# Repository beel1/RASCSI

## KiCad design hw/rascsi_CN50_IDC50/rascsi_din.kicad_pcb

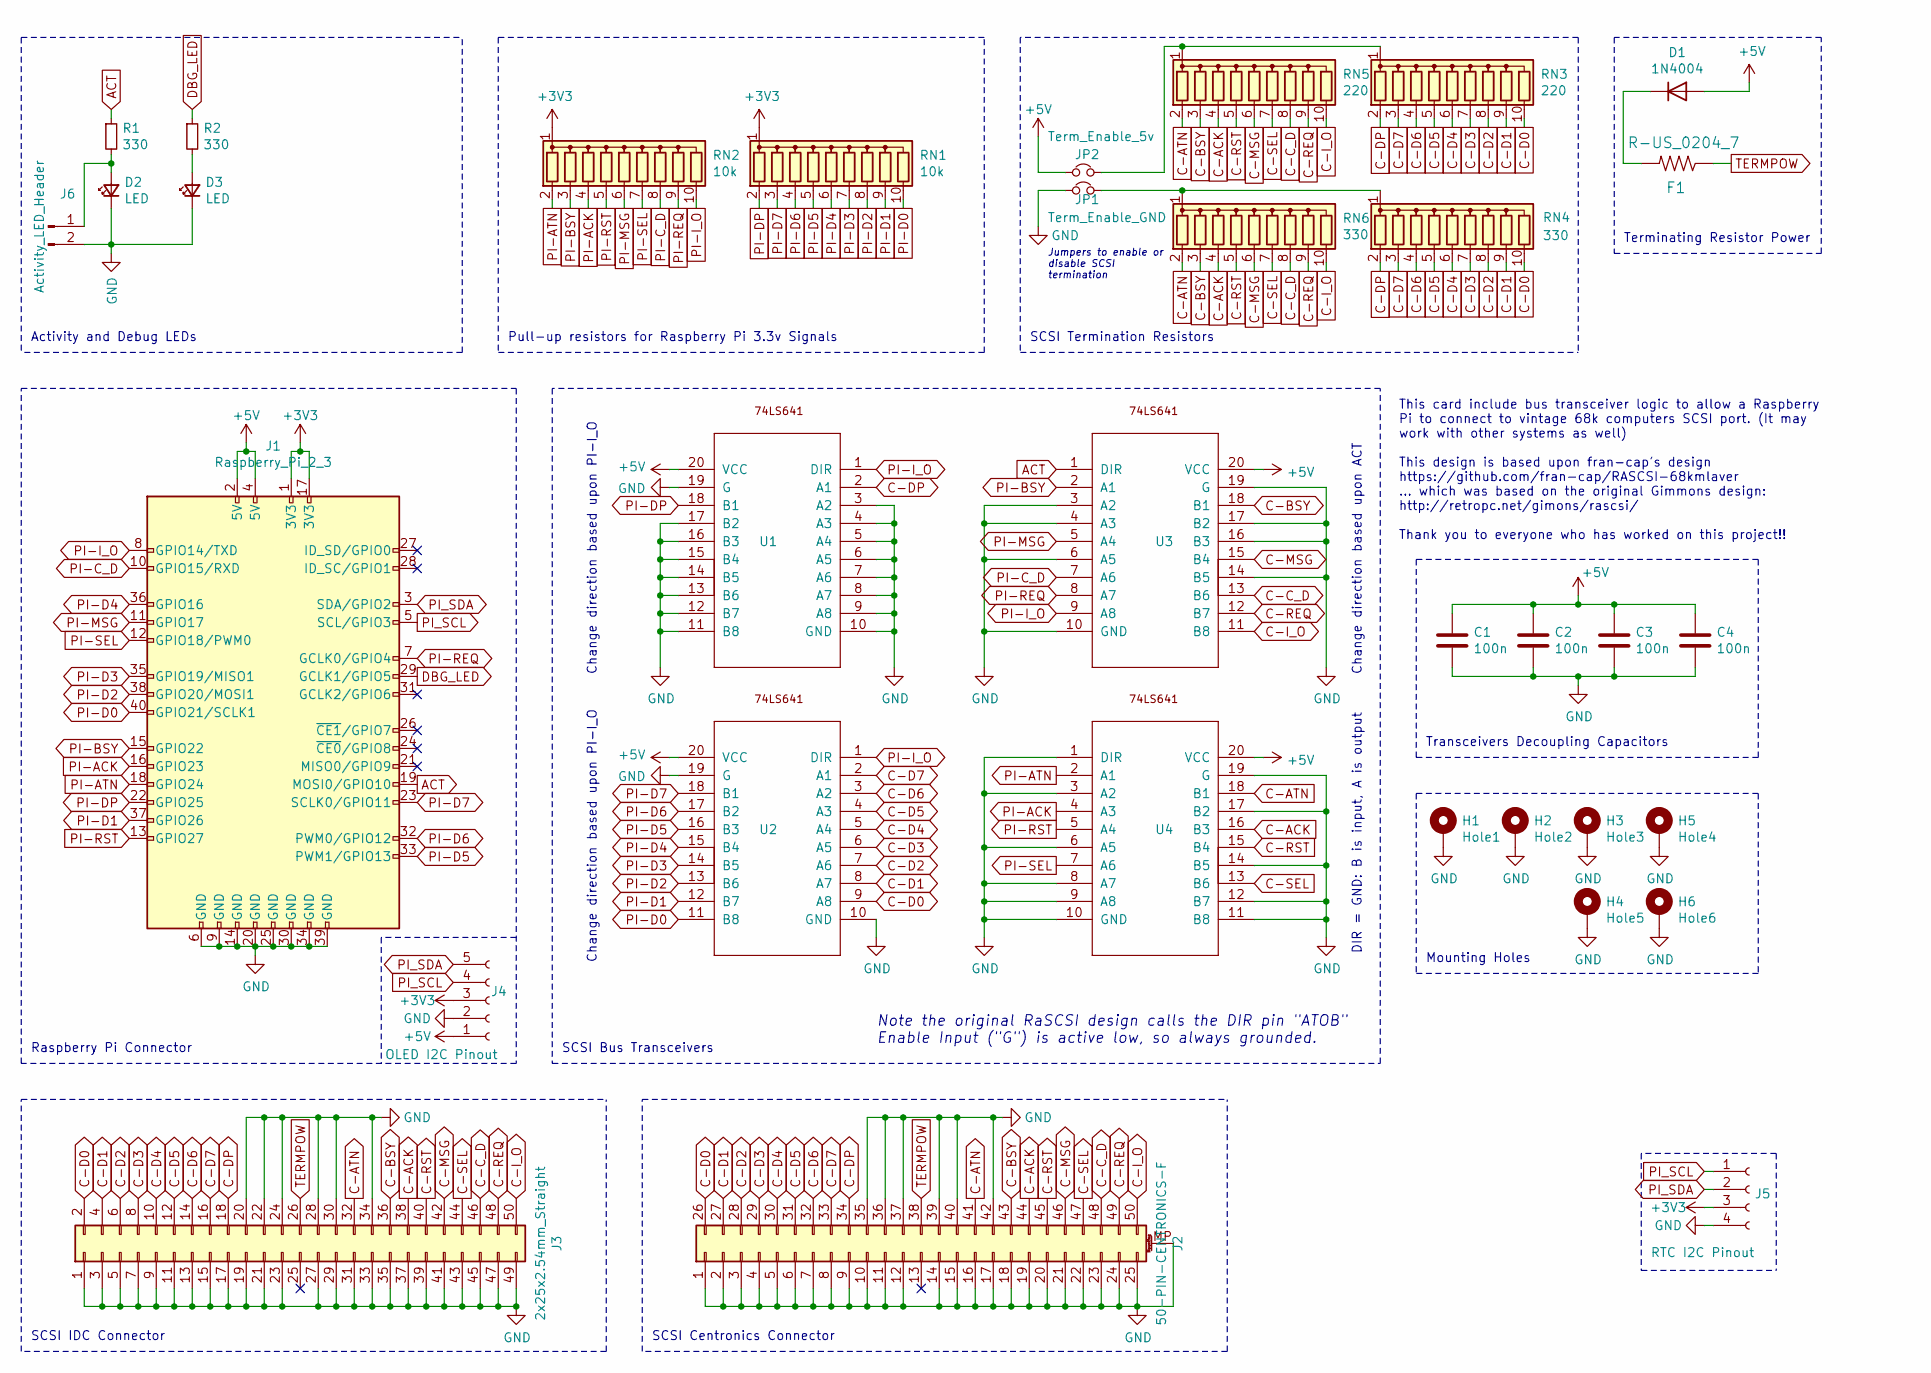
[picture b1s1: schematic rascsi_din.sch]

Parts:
C1, C2, C3, C4: 100n; C_Disc_D5.0mm_W2.5mm_P2.50mm
D1: 1N4004; D_DO-41_SOD81_P10.16mm_Horizontal
D2, D3: LED; LED_D5.0mm
F1: R-US_0204_7; 0204_7
H1: Hole1; MountingHole_2.7mm_M2.5_Pad_Via
H2: Hole2; MountingHole_2.7mm_M2.5_Pad_Via
H3: Hole3; MountingHole_2.7mm_M2.5_Pad_Via
H4: Hole5; MountingHole_2.7mm_M2.5_Pad_Via
H5: Hole4; MountingHole_2.7mm_M2.5_Pad_Via
H6: Hole6; MountingHole_2.7mm_M2.5_Pad_Via
J1: Raspberry_Pi_2_3; Socket_Strip_Straight_2x20_Pitch2.54mm
J2: 50-PIN-CENTRONICS-F
J3: 2x25x2.54mm_Straight; Multicomp_MC9A12-5034_2x25x2.54mm_Straight
J4: OLED I2C Pinout; Socket_Strip_Straight_1x05_Pitch2.54mm
J5: RTC I2C Pinout; Socket_Strip_Straight_1x04_Pitch2.54mm
J6: Activity_LED_Header; Pin_Header_Straight_1x02_Pitch2.54mm
JP1: Term_Enable_GND; Pin_Header_Straight_1x02_Pitch2.54mm
JP2: Term_Enable_5v; Pin_Header_Straight_1x02_Pitch2.54mm
R1, R2: 330; R_Axial_DIN0204_L3.6mm_D1.6mm_P7.62mm_Horizontal
RN1, RN2: 10k; R_Array_SIP10
RN3, RN5: 220; R_Array_SIP10
RN4, RN6: 330; R_Array_SIP10
U1, U2, U3, U4: SN74LS641-1C; DIP-20_W7.62mm

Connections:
+3V3: J1.1 (3V3), J1.17 (3V3), J4.3, J5.3, RN1.1 (common), RN2.1 (common)
+5V: C1.1, C2.1, C3.1, C4.1, D1.2 (A), J1.2 (5V), J1.4 (5V), J4.1, JP2.1, U1.20 (VCC), U2.20 (VCC), U3.20 (VCC), U4.20 (VCC)
ACT: J1.19 (MOSI0/GPIO10), R1.1, U3.1 (DIR)
C-ACK: J2.44, J3.38, RN5.4 (R3), RN6.4 (R3), U4.16 (B3)
C-ATN: J2.41, J3.32, RN5.2 (R1), RN6.2 (R1), U4.18 (B1)
C-BSY: J2.43, J3.36, RN5.3 (R2), RN6.3 (R2), U3.18 (B1)
C-C_D: J2.48, J3.46, RN5.8 (R7), RN6.8 (R7), U3.13 (B6)
C-D0: J2.26, J3.2, RN3.10 (R9), RN4.10 (R9), U2.9 (A8)
C-D1: J2.27, J3.4, RN3.9 (R8), RN4.9 (R8), U2.8 (A7)
C-D2: J2.28, J3.6, RN3.8 (R7), RN4.8 (R7), U2.7 (A6)
C-D3: J2.29, J3.8, RN3.7 (R6), RN4.7 (R6), U2.6 (A5)
C-D4: J2.30, J3.10, RN3.6 (R5), RN4.6 (R5), U2.5 (A4)
C-D5: J2.31, J3.12, RN3.5 (R4), RN4.5 (R4), U2.4 (A3)
C-D6: J2.32, J3.14, RN3.4 (R3), RN4.4 (R3), U2.3 (A2)
C-D7: J2.33, J3.16, RN3.3 (R2), RN4.3 (R2), U2.2 (A1)
C-DP: J2.34, J3.18, RN3.2 (R1), RN4.2 (R1), U1.2 (A1)
C-I_O: J2.50, J3.50, RN5.10 (R9), RN6.10 (R9), U3.11 (B8)
C-MSG: J2.46, J3.42, RN5.6 (R5), RN6.6 (R5), U3.15 (B4)
C-REQ: J2.49, J3.48, RN5.9 (R8), RN6.9 (R8), U3.12 (B7)
C-RST: J2.45, J3.40, RN5.5 (R4), RN6.5 (R4), U4.15 (B4)
C-SEL: J2.47, J3.44, RN5.7 (R6), RN6.7 (R6), U4.13 (B6)
DBG_LED: J1.29 (GCLK1/GPIO5), R2.1
GND: C1.2, C2.2, C3.2, C4.2, D2.1 (K), D3.1 (K), H1.1, H2.1, H3.1, H4.1, H5.1, H6.1, J1.6 (GND), J1.9 (GND), J1.14 (GND), J1.20 (GND), J1.25 (GND), J1.30 (GND), J1.34 (GND), J1.39 (GND), J2.1, J2.2, J2.3, J2.4, J2.5, J2.6, J2.7, J2.8, J2.9, J2.10, J2.11, J2.12, J2.14, J2.15, J2.16, J2.17, J2.18, J2.19, J2.20, J2.21, J2.22, J2.23, J2.24, J2.25, J2.35, J2.36, J2.37, J2.39, J2.40, J2.42, J2.MP (MountPin), J3.1, J3.3, J3.5, J3.7, J3.9, J3.11, J3.13, J3.15, J3.17, J3.19, J3.20, J3.21, J3.22, J3.23, J3.24, J3.27, J3.28, J3.29, J3.30, J3.31, J3.33, J3.34, J3.35, J3.37, J3.39, J3.41, J3.43, J3.45, J3.47, J3.49, J4.2, J5.4, J6.2, JP1.1, U1.3 (A2), U1.4 (A3), U1.5 (A4), U1.6 (A5), U1.7 (A6), U1.8 (A7), U1.9 (A8), U1.10 (GND), U1.11 (B8), U1.12 (B7), U1.13 (B6), U1.14 (B5), U1.15 (B4), U1.16 (B3), U1.17 (B2), U1.19 (G), U2.10 (GND), U2.19 (G), U3.3 (A2), U3.4 (A3), U3.6 (A5), U3.10 (GND), U3.14 (B5), U3.16 (B3), U3.17 (B2), U3.19 (G), U4.1 (DIR), U4.3 (A2), U4.6 (A5), U4.8 (A7), U4.9 (A8), U4.10 (GND), U4.11 (B8), U4.12 (B7), U4.14 (B5), U4.17 (B2), U4.19 (G)
unnamed: D1.1 (K), F1.2
unnamed: D2.2 (A), J6.1, R1.2
unnamed: D3.2 (A), R2.2
unnamed: JP1.2, RN4.1 (common), RN6.1 (common)
unnamed: JP2.2, RN3.1 (common), RN5.1 (common)
PI-ACK: J1.16 (GPIO23), RN2.4 (R3), U4.4 (A3)
PI-ATN: J1.18 (GPIO24), RN2.2 (R1), U4.2 (A1)
PI-BSY: J1.15 (GPIO22), RN2.3 (R2), U3.2 (A1)
PI-C_D: J1.10 (GPIO15/RXD), RN2.8 (R7), U3.7 (A6)
PI-D0: J1.40 (GPIO21/SCLK1), RN1.10 (R9), U2.11 (B8)
PI-D1: J1.37 (GPIO26), RN1.9 (R8), U2.12 (B7)
PI-D2: J1.38 (GPIO20/MOSI1), RN1.8 (R7), U2.13 (B6)
PI-D3: J1.35 (GPIO19/MISO1), RN1.7 (R6), U2.14 (B5)
PI-D4: J1.36 (GPIO16), RN1.6 (R5), U2.15 (B4)
PI-D5: J1.33 (PWM1/GPIO13), RN1.5 (R4), U2.16 (B3)
PI-D6: J1.32 (PWM0/GPIO12), RN1.4 (R3), U2.17 (B2)
PI-D7: J1.23 (SCLK0/GPIO11), RN1.3 (R2), U2.18 (B1)
PI-DP: J1.22 (GPIO25), RN1.2 (R1), U1.18 (B1)
PI-I_O: J1.8 (GPIO14/TXD), RN2.10 (R9), U1.1 (DIR), U2.1 (DIR), U3.9 (A8)
PI-MSG: J1.11 (GPIO17), RN2.6 (R5), U3.5 (A4)
PI-REQ: J1.7 (GCLK0/GPIO4), RN2.9 (R8), U3.8 (A7)
PI-RST: J1.13 (GPIO27), RN2.5 (R4), U4.5 (A4)
PI-SEL: J1.12 (GPIO18/PWM0), RN2.7 (R6), U4.7 (A6)
PI_SCL: J1.5 (SCL/GPIO3), J4.4, J5.1
PI_SDA: J1.3 (SDA/GPIO2), J4.5, J5.2
TERMPOW: F1.1, J2.38, J3.26

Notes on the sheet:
Note the original RaSCSI design calls the DIR pin "ATOB" Enable Input ("G") is active low, so always grounded.
Pull-up resistors for Raspberry Pi 3.3v Signals
SCSI Termination Resistors
Raspberry Pi Connector
SCSI Bus Transceivers
Change direction based upon PI-I_O
DIR = GND: B is input, A is output
SCSI IDC Connector
This card include bus transceiver logic to allow a Raspberry Pi to connect to vintage 68k computers SCSI port. (It may work with other systems as well) This design is based upon fran-cap's design https://github.com/fran-cap/RASCSI-68kmlaver ... which was based on the original Gimmons design: http:/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
Mounting Holes
Jumpers to enable or disable SCSI termination
Change direction based upon ACT
Activity and Debug LEDs
Transceivers Decoupling Capacitors
Terminating Resistor Power
SCSI Centronics Connector

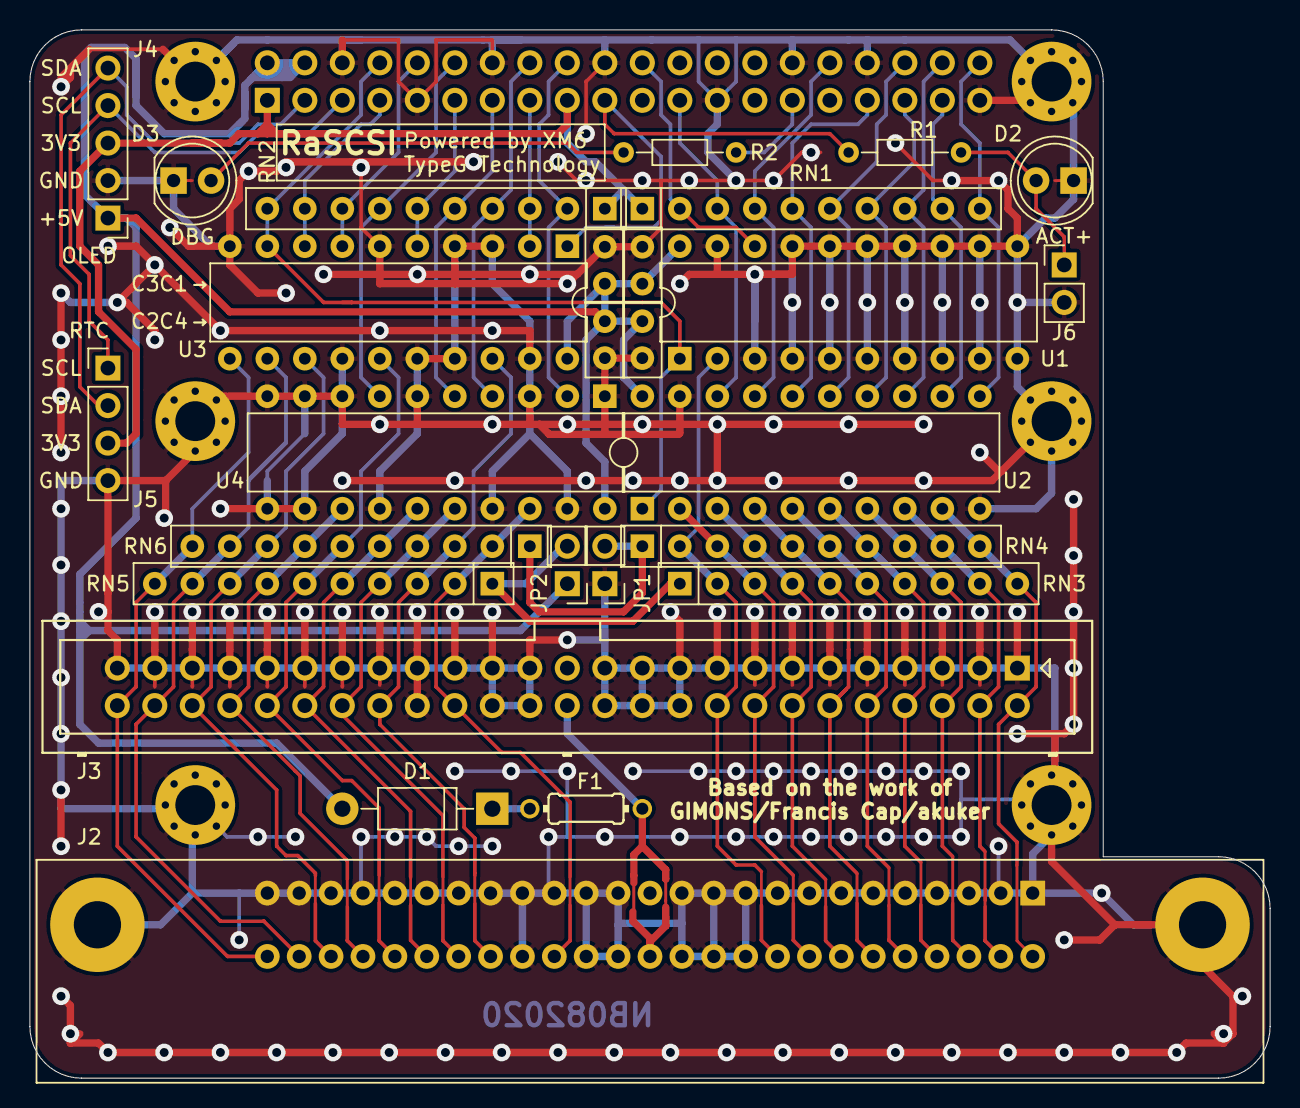
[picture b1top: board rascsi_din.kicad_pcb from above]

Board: 2 copper layers, 84.0 x 71.0 mm, 34 parts (0 on the bottom side), 49 nets.

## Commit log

2021-11-03 Added missing dependency to easyinstall
2021-11-03 Revert "Added missing dependency to easyinstall"
    This reverts commit 0e14a206a0e12b47003db191db0d7d1f308bde72.
2021-11-07 Fix issue 422 (#425)
    * Use the effective filename when checking for duplicates
    * Fixed check for asynchronous notifications
    * Added additional filename check
    * Applied fix also for attach
2021-11-08 DaynaPort: Ignore commands with a bogus control value (#433)
    All traffic from the DaynaPort will have a control value of 0xc0 or
    0x80, so any commands that don't should be ignored.
    This helps the Mac Plus which will try to READ(6) from the DaynaPort
    device if it's attached at boot and then try to interpret the
    ethernet packet as hard drive data and crash.
    See issue akuker#419
2021-11-08 DaynaPort: Remove scsi_cmd_read_6_t struct, it was not correct (#435)
    The DWORDs in `cdb *` are not raw packed data from the wire, they
    are manually copied in a previous function. Trying to cast that
    unpacked, aligned-on-byte-boundary data into the packed
    scsi_cmd_read_6_t structure is not correct and does not put the
    correct DWORDs into the proper fields.
    Just do away with this struct and refer to the 2 cdb DWORDs (opcode
2021-11-13 IMAGE_FILE_INFO used hostname instead of filename (#457)
2021-11-13 Add Centronics 50 RaSCSI Target board
    Based on /RASCSI/hw/rascsi_1p6/ using only through-hole components
    Centronics 50 (SCSI-1) footprint based on SparkFun connectors library
    CAD software is KiCAD 5.1.6-1
    Non-standard GPIO pins assignment
    Added headers for I2C RTC module and front panel ACTivity LED
2021-11-14 Add Centronics 50 target board BOM
2021-11-14 Import source code of baremetal version 1.52
    See http://retropc.net/gimons/rascsi/index.html
2021-12-02 Add BEEL1 connection type and assignments to gpiobus.h #2
